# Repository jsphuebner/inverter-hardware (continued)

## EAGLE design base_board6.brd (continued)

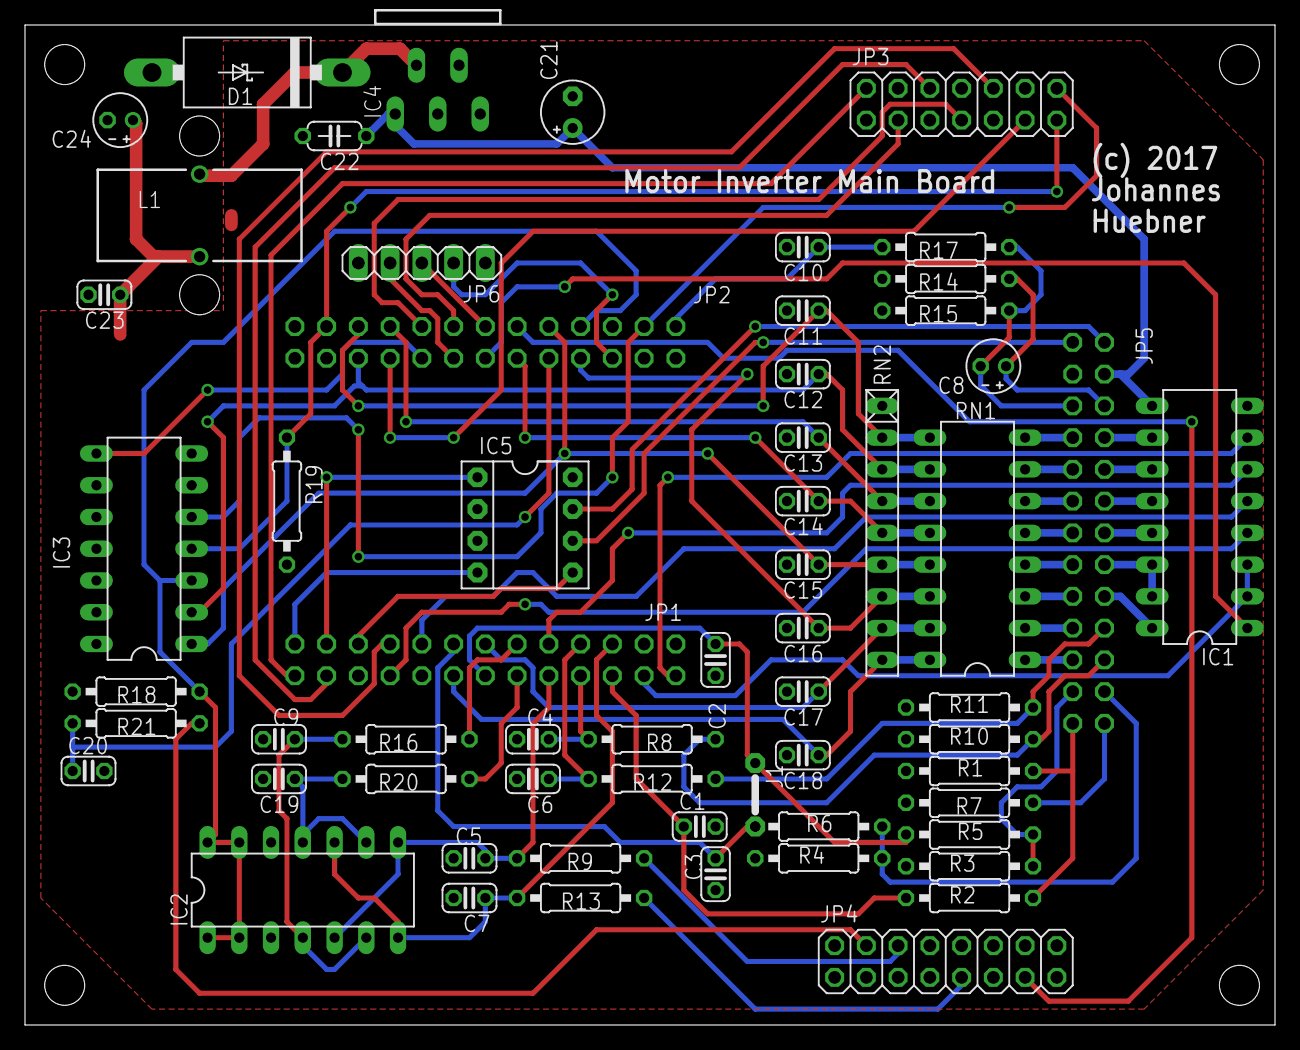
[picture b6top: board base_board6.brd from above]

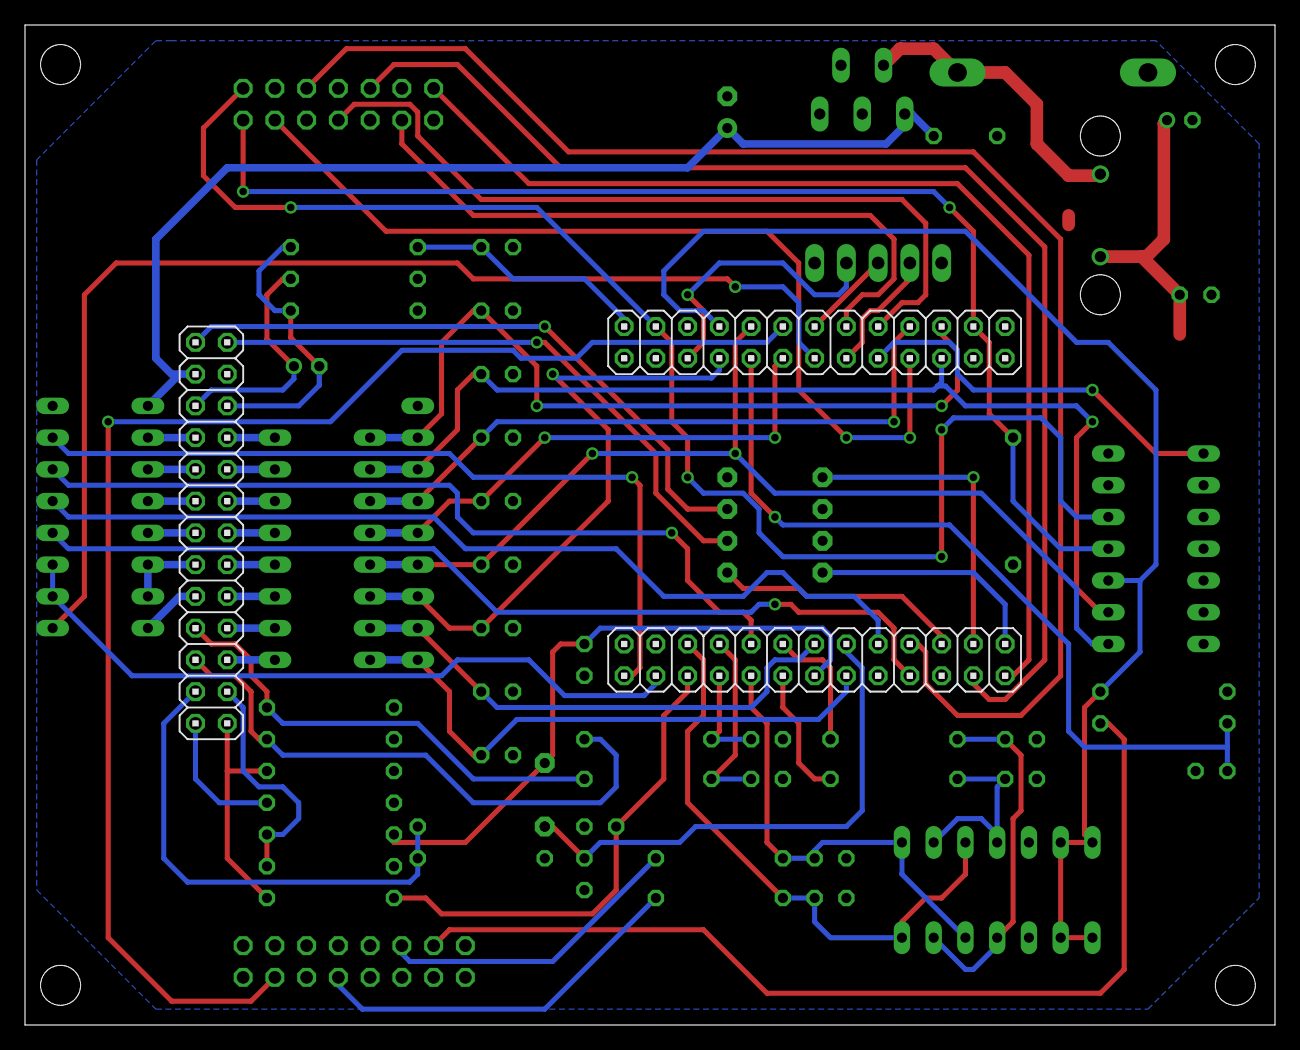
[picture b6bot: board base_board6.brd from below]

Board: 2 copper layers, 100.0 x 80.0 mm, 61 parts (3 on the bottom side), 75 nets.

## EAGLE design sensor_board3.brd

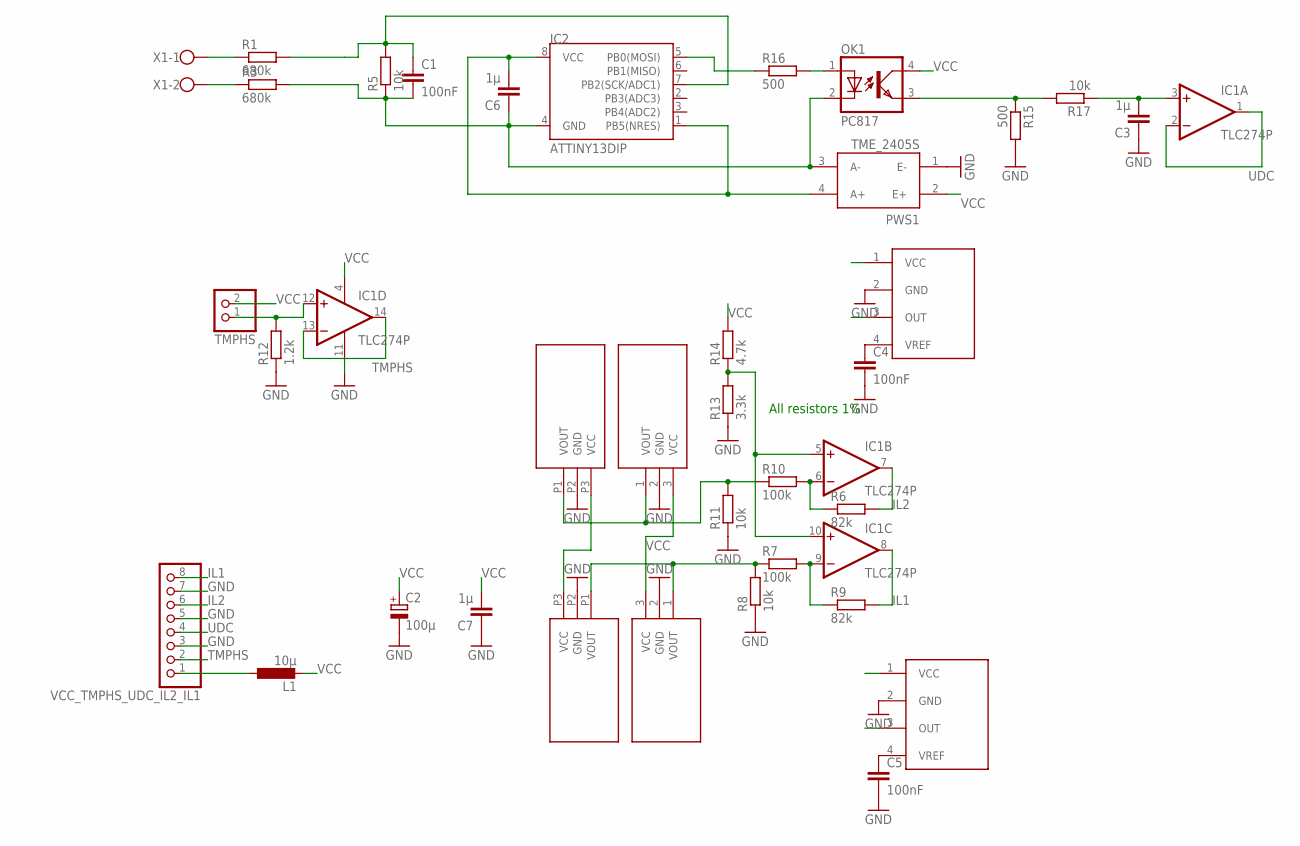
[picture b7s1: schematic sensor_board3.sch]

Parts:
C1, C4, C5: 100nF; C025-024X044
C2: 100µ; E2,5-6E
C3, C6, C7: 1µ; C025-024X044
IC1: TLC274P; DIL14
IC2: ATTINY13DIP; DIP08
L1: 10µ; 0207/12
OK1: PC817; DIL04
PWS1: TME_2405S; TMEXXXXS
R1, R3: 680k; 0207/10
R5, R8, R11, R17: 10k; 0207/10
R6, R9: 82k; 0207/10
R7, R10: 100k; 0207/10
R12: 1.2k; 0207/10
R13: 3.3k; 0207/10
R14: 4.7k; 0207/10
R15, R16: 500; 0207/10
TMPHS: PINHD-1X2; 1X02
U$1, U$2: TAMURA_L01Z_S05
U$3, U$4: HTFS
U$5, U$6: TAMURA_L06P_S05L06P; TAMURA_L06P_S05
VCC_TMPHS_UDC_IL2_IL1: PINHD-1X8; 1X08
X1: W237-102

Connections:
GND: C2.-, C3.1, C4.2, C5.2, C7.1, IC1.11 (V-), PWS1.1 (E-), R8.1, R11.1, R12.1, R13.1, R15.2, U$1.2 (GND), U$2.2 (GND), U$3.2 (GND), U$4.2 (GND), U$5.P2 (GND), U$6.P2 (GND), VCC_TMPHS_UDC_IL2_IL1.3, VCC_TMPHS_UDC_IL2_IL1.5, VCC_TMPHS_UDC_IL2_IL1.7
GND2: C1.2, C6.1, IC2.4 (GND), OK1.2 (C), PWS1.3 (A-), R3.2, R5.1
IL1: IC1.8 (OUT), R9.2, VCC_TMPHS_UDC_IL2_IL1.8
IL2: IC1.7 (OUT), R6.2, VCC_TMPHS_UDC_IL2_IL1.6
unnamed: IC1.5 (+IN), IC1.10 (+IN), R13.2, R14.1
unnamed: C1.1, IC2.7 (PB2(SCK/ADC1)), R1.2, R5.2
unnamed: R1.1, X1.1
unnamed: R3.1, X1.2
unnamed: L1.1, VCC_TMPHS_UDC_IL2_IL1.1
unnamed: IC1.9 (-IN), R7.2, R9.1
unnamed: IC1.6 (-IN), R6.1, R10.2
unnamed: OK1.3 (EMIT), R15.1, R17.2
unnamed: C4.1, U$3.4 (VREF)
unnamed: C5.1, U$4.4 (VREF)
unnamed: IC1.12 (+IN), R12.2, TMPHS.1
unnamed: OK1.1 (A), R16.2
unnamed: IC2.5 (PB0(MOSI)), R16.1
unnamed: C3.2, IC1.3 (+IN), R17.1
TMPHS: IC1.13 (-IN), IC1.14 (OUT), VCC_TMPHS_UDC_IL2_IL1.2
UDC: IC1.1 (OUT), IC1.2 (-IN), VCC_TMPHS_UDC_IL2_IL1.4
VCC: C2.+, C7.2, IC1.4 (V+), L1.2, OK1.4 (COL), PWS1.2 (E+), R14.2, TMPHS.2, U$1.3 (VCC), U$2.3 (VCC), U$3.1 (VCC), U$4.1 (VCC), U$5.P3 (VCC), U$6.P3 (VCC)
VCC2: C6.2, IC2.1 (PB5(NRES)), IC2.8 (VCC), PWS1.4 (A+)
VOUT1: R7.1, R8.2, U$2.1 (VOUT), U$4.3 (OUT), U$6.P1 (VOUT)
VOUT2: R10.1, R11.2, U$1.1 (VOUT), U$3.3 (OUT), U$5.P1 (VOUT)

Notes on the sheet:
All resistors 1%

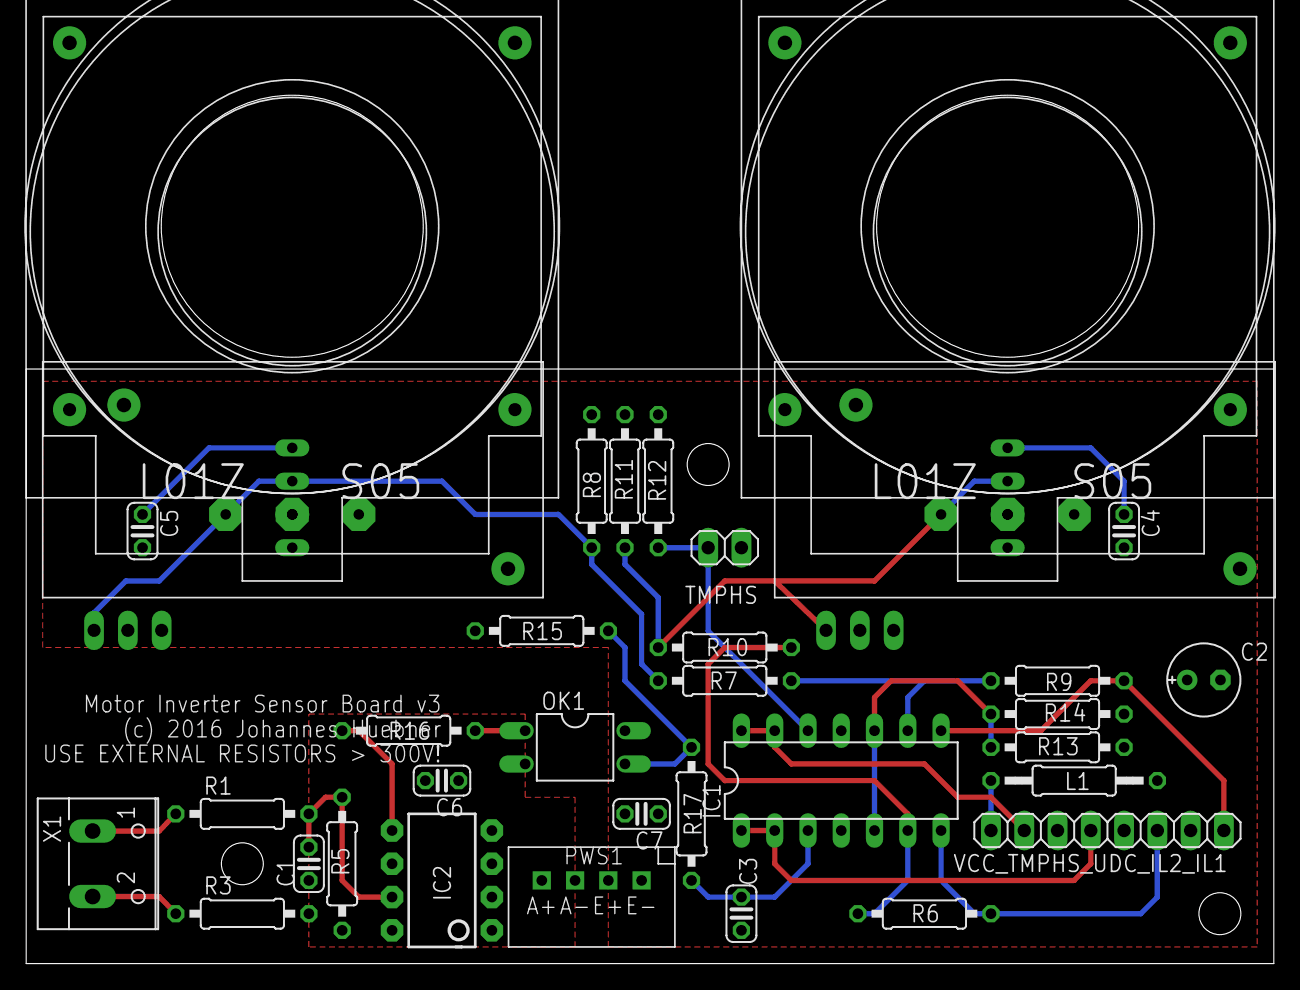
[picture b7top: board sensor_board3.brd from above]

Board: 2 copper layers, 95.2 x 45.4 mm, 36 parts (0 on the bottom side), 24 nets.

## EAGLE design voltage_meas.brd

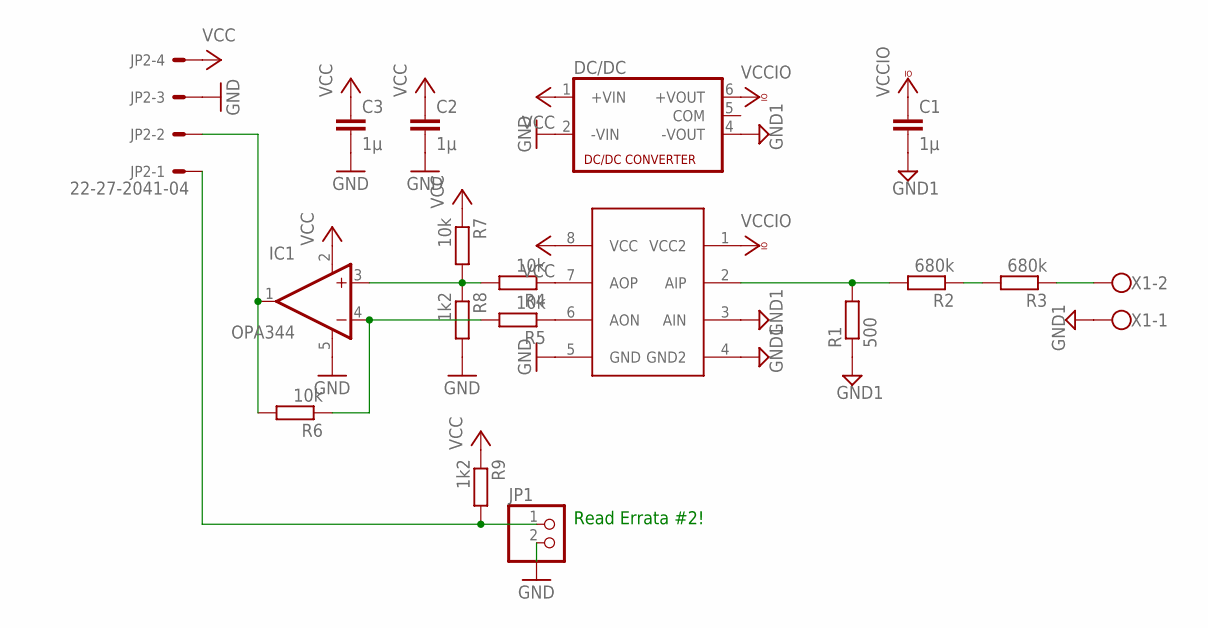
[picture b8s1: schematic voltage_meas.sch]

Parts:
C1, C2, C3: 1µ; C025-024X044
DC/DC: MEV3; NMA
IC1: OPA344; SOT23-5
IC2: SI8920; DIP8
JP1: PINHD-1X2; 1X02
JP2: 22-27-2041-04; 6410-04
R1: 500; 0207/10
R2, R3: 680k; 0207/10
R4, R5, R6, R7: 10k; 0207/10
R8, R9: 1k2; 0207/10
X1: W237-102

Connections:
GND: C2.2, C3.2, DC/DC.2 (-VIN), IC1.5 (V+), IC2.5 (GND), JP1.2, JP2.3, R8.2
GND1: C1.2, DC/DC.4 (-VOUT), IC2.3 (AIN), IC2.4 (GND2), R1.1, X1.1
unnamed: IC2.2 (AIP), R1.2, R2.2
unnamed: R2.1, R3.2
unnamed: R3.1, X1.2
unnamed: IC2.7 (AOP), R4.1
unnamed: IC2.6 (AON), R5.1
unnamed: IC1.1 (OUT), JP2.2, R6.2
unnamed: IC1.4 (-IN), R5.2, R6.1
unnamed: IC1.3 (+IN), R4.2, R7.2, R8.1
unnamed: JP1.1, JP2.1, R9.2
VCC: C2.1, C3.1, DC/DC.1 (+VIN), IC1.2 (V-), IC2.8 (VCC), JP2.4, R7.1, R9.1
VCCIO: C1.1, DC/DC.6 (+VOUT), IC2.1 (VCC2)

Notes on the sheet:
Read Errata #2!

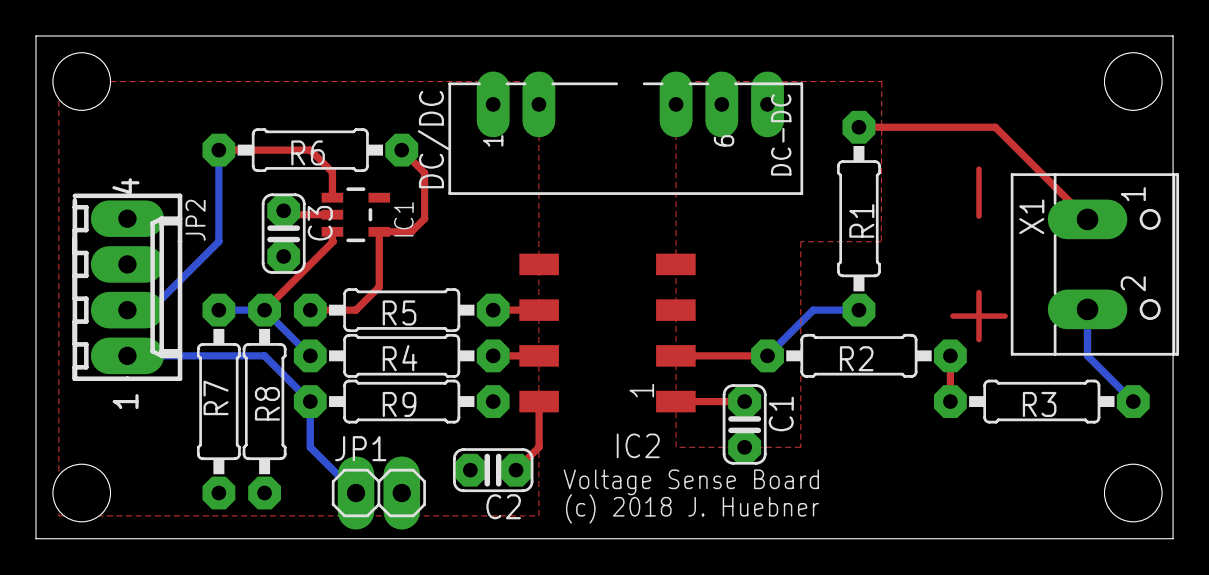
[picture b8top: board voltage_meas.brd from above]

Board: 2 copper layers, 63.2 x 27.9 mm, 18 parts (0 on the bottom side), 13 nets.

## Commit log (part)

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2018-11-01 Added openinverter library
    Contains foot print for SMD mainboard. Lets you design an adapter board
2018-11-09 Changed a component value and added annotations
2018-11-10 Added credits for drawing
2018-11-30 Label corrections
    Corrected swapped labels of IC2 and IC8. Added part number of IC9
2018-12-03 Added missing part numbers
2019-01-03 Added gate driver schematics and layout
2019-05-15 Added leaf adapter design file
2020-01-03 Added openinverter V3 SMD mainboard revision 1.2
2020-01-03 Added revision info
2020-01-25 Small changed for compatibility with JLCPCBs parts library
2020-01-25 Added Gerber, BOM and placement file - NAND gate still has wrong foot print!
2020-01-25 Replaced SOT23-6 by SC70-6 foot print for IC9 Moved copyright info away from trace fixed font of silk screen
2020-06-29 New mainboard v3.4 Using TagConnect for programming Using FET for dcsw output Optimized BOM Added solder bridges for optional resistors
2020-07-15 Added Prius manufacturing files and schematic
2020-08-30 Added labels to IC7 and IC5
2021-04-08 Added phase module
2021-04-08 force .fpc crlf
2021-11-19 Updated Leaf adapter to SMT
2021-11-19 Added Leaf adapter BOM and PLC
2022-04-09 Added mini mainboard
2022-07-05 Added 10k resistor to CAN transceiver RS pin
2022-07-20 Updated pdf
